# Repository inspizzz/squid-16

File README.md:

<div align="center">

# Squid-16

**An open-source, 16-channel dry-electrode EEG sensor on one 40 mm board.**

Eighteen spring-loaded pins, two 24-bit converters, an on-board ESP32-C3 and Bluetooth LE.
No gel, no cap, no separate controller.

<sub>3D render from the design files, not a photograph. No board has been built yet.</sub>

[Build one](docs/BUILD.md) · [How it works](docs/DESIGN.md) · [Simulation results](sim/results/report.md) · [Get one](#get-one) · [Cost](#what-it-costs)

</div>

> **Not a medical device.** This is an experimenter's board. It has no
> isolation from its power supply: wear it only while it runs from a battery or
> power bank, never while it is connected to a computer or a wall charger.

> **Status: revision B, not yet built.** The design passes KiCad's electrical
> and design-rule checks, the firmware compiles and passes its PC-side tests,
> and the wiring has been checked in simulation, but no board has been
> manufactured or powered. Expect to debug. There are no measured noise or
> performance figures yet. See
> [what has and has not been verified](#what-has-been-verified).

## What it is

| | |
|---|---|
| Channels | 16, plus a reference pin and a bias pin, in one 30 mm cluster |
| Electrodes | 18 surface-mount spring pins, 4 mm tip, 6.5 mm apart |
| Converters | 2 x TI ADS131M08, 24-bit, all channels sampled at the same instant |
| Sample rate | 250 samples/s nominal (8.192 MHz clock, highest oversampling setting; not yet measured) |
| Reference | Buffered by a low-noise op-amp (can be bypassed) |
| Processor and radio | Espressif ESP32-C3-WROOM-02 module, soldered on |
| Link | Bluetooth LE, one 51-byte packet per sample |
| Board | 40 mm round, 4 layers, 1.0 mm thick; parts on top, pins underneath |
| Power and flashing | USB-C on the board, 5 V from a power bank |

Squid-16 is an independent design inspired by the PiEEG "Octopus 16" idea of
putting the whole montage, reference included, on one small board. It shares no
design files or code with that product (which publishes neither schematics nor
a licence); it is drawn from the component datasheets. Its data stream uses the
same packet layout, so viewers written for that format can read it.
[How it differs](docs/DESIGN.md#how-it-differs-from-the-board-that-inspired-it).

This project is not affiliated with, endorsed by or supported by PiEEG.
"PiEEG" and "Octopus 16" are names used by their owner and appear here only
to say what inspired this design.

Revision A (32 mm, with a plug-in Seeed XIAO ESP32-S3 instead of an on-board
module) is kept under the git tag `rev-A`.

## Repository map

```
README.md            you are here
LICENSE              which licence covers what
docs/
  BUILD.md           order, assemble, flash, first signal: start here to make one
  DESIGN.md          how the circuit works, pin maps, limits, open questions
  img/               renders and layer pictures
hardware/
  squid16.kicad_pro / .kicad_sch / .kicad_pcb    open these in KiCad 9
  lib/               the two project footprints (spring pin, radio module) and a 3D model of the pin
  production/        ready-to-upload gerbers, BOM, placement files, schematic PDF
  scripts/           the design as code: one file in, schematic + board out
firmware/
  squid16/          PlatformIO project for the on-board ESP32-C3
  test/              PC-side tests of the driver against a simulated converter
software/
  squid16.py        record to CSV over Bluetooth
sim/
  run_all.py         simulate this board; results in sim/results/report.md
```

## Get one

**Nobody sells built Squid-16 boards.** This is a design you have made for
you. There are three ways to end up holding one:

| Route | What you do | Skill needed |
|---|---|---|
| **Have it built** (easiest) | Upload [`hardware/production/squid16-pcbway.zip`](hardware/production/squid16-pcbway.zip) to a turnkey assembler such as PCBWay. It contains the gerbers, a parts list with manufacturer part numbers, placement files and a notes file. They make the board, buy the parts and solder them. You flash the firmware over USB-C. | None beyond placing an order |
| **Have the top side built, fit the pins yourself** | Same package, ask for top side only. Solder the 18 spring pins with an ordinary iron (one large pad each). | Basic soldering |
| **Build it all yourself** | Order bare boards from the gerbers and follow [docs/BUILD.md](docs/BUILD.md). | Fine-pitch surface-mount soldering, hot air |

After that: plug in USB-C, run `pio run -t upload` in `firmware/squid16`,
power it from a power bank and run `python3 software/squid16.py`.
[docs/BUILD.md](docs/BUILD.md) has every step.

If you would rather buy a finished unit, open an issue saying so. There is no
promise that a batch will be made, but it is the only way interest gets
counted.

Because this revision is untested, order the minimum (five boards, two
assembled) and expect the first one to need debugging.

## What it costs

Figures for **five bare boards with two assembled**, the smallest sensible
order. The PCBWay figures are what its online calculator showed for this
design's gerbers on 10 November 2026, before their engineers' review; the rest
are estimates. Import VAT and duty are extra.

| Item | Cost (USD) | Source |
|---|---|---|
| 5 bare boards: 4 layers, 1.0 mm, ENIG, 5-day build | 62 | PCBWay calculator |
| Assembly labour, 2 boards, one or both sides | 88 | PCBWay calculator |
| Courier shipping | about 29, offset by a first-order discount at the time | PCBWay calculator |
| Components for 2 boards, excluding the spring pins | 80 - 110 | estimate from distributor prices |
| 36 Mill-Max spring pins (18 per board) | about 145 | DigiKey list price, about 4 each |
| **Two working boards, Mill-Max pins** | **about 375 - 405** | |
| **Per board** | **about 190 - 200** | |

Ways to spend less:

- Generic 4 x 11 mm surface-mount pogo pins fit the same pads and cost a
  small fraction of the Mill-Max part. Untested, like everything else here.
- Lead-free HASL instead of ENIG roughly halves the bare-board price (32
  instead of 62), at the cost of less flat pads.
- The three spare bare boards cost only parts to populate later.

## Change it

The whole board is generated from one Python file,
[`hardware/scripts/design.py`](hardware/scripts/design.py): every part, net and
position. Edit it and run

```
hardware/scripts/build.sh
```

to regenerate the schematic, place and route the board, run the checks and
write new fabrication files (needs KiCad 9 and numpy; routing takes 6 to 12
minutes). The router is a simple one written for this board and it does not
succeed every time: of three full rebuilds of this exact design, one connected
everything, and that is the board committed here. When it fails it says so and
puts the previous board back; run it again or nudge a part. You can also just
open the KiCad files and edit them by hand, but
then stop using the generator, because it overwrites them.

## What has been verified

| Check | Result |
|---|---|
| Schematic electrical rules (KiCad ERC, all severities) | 0 violations |
| Board design rules (KiCad DRC, all severities) | 0 violations, 0 unconnected |
| Schematic and board agree (DRC parity, plus a pin-by-pin netlist comparison with `design.py`) | 0 differences |
| Rebuilding the board from `design.py` gives a complete board every time | **no**: 1 of 3 attempts; the committed board is the complete one |
| Firmware driver and packet code against a simulated ADS131M08 (`firmware/test/run.sh`) | pass |
| Firmware builds for the ESP32-C3 (PlatformIO, Arduino core, NimBLE-Arduino) | builds, 753 kB flash |
| Recorder packet decoder (`squid16.py --selftest`) | pass |
| Wiring traced from the PCB copper against the firmware's pins and channel order ([simulation](sim/results/report.md)) | 16 of 16 channels in the right place |
| A manufactured board | **not done** |
| Firmware on real hardware, Bluetooth range and throughput, noise, signal quality | **not done** |

## Licence

Hardware: CERN-OHL-P-2.0. Firmware and software: MIT. Documentation: CC-BY-4.0.
See [LICENSE](LICENSE). You may build, change and sell it.

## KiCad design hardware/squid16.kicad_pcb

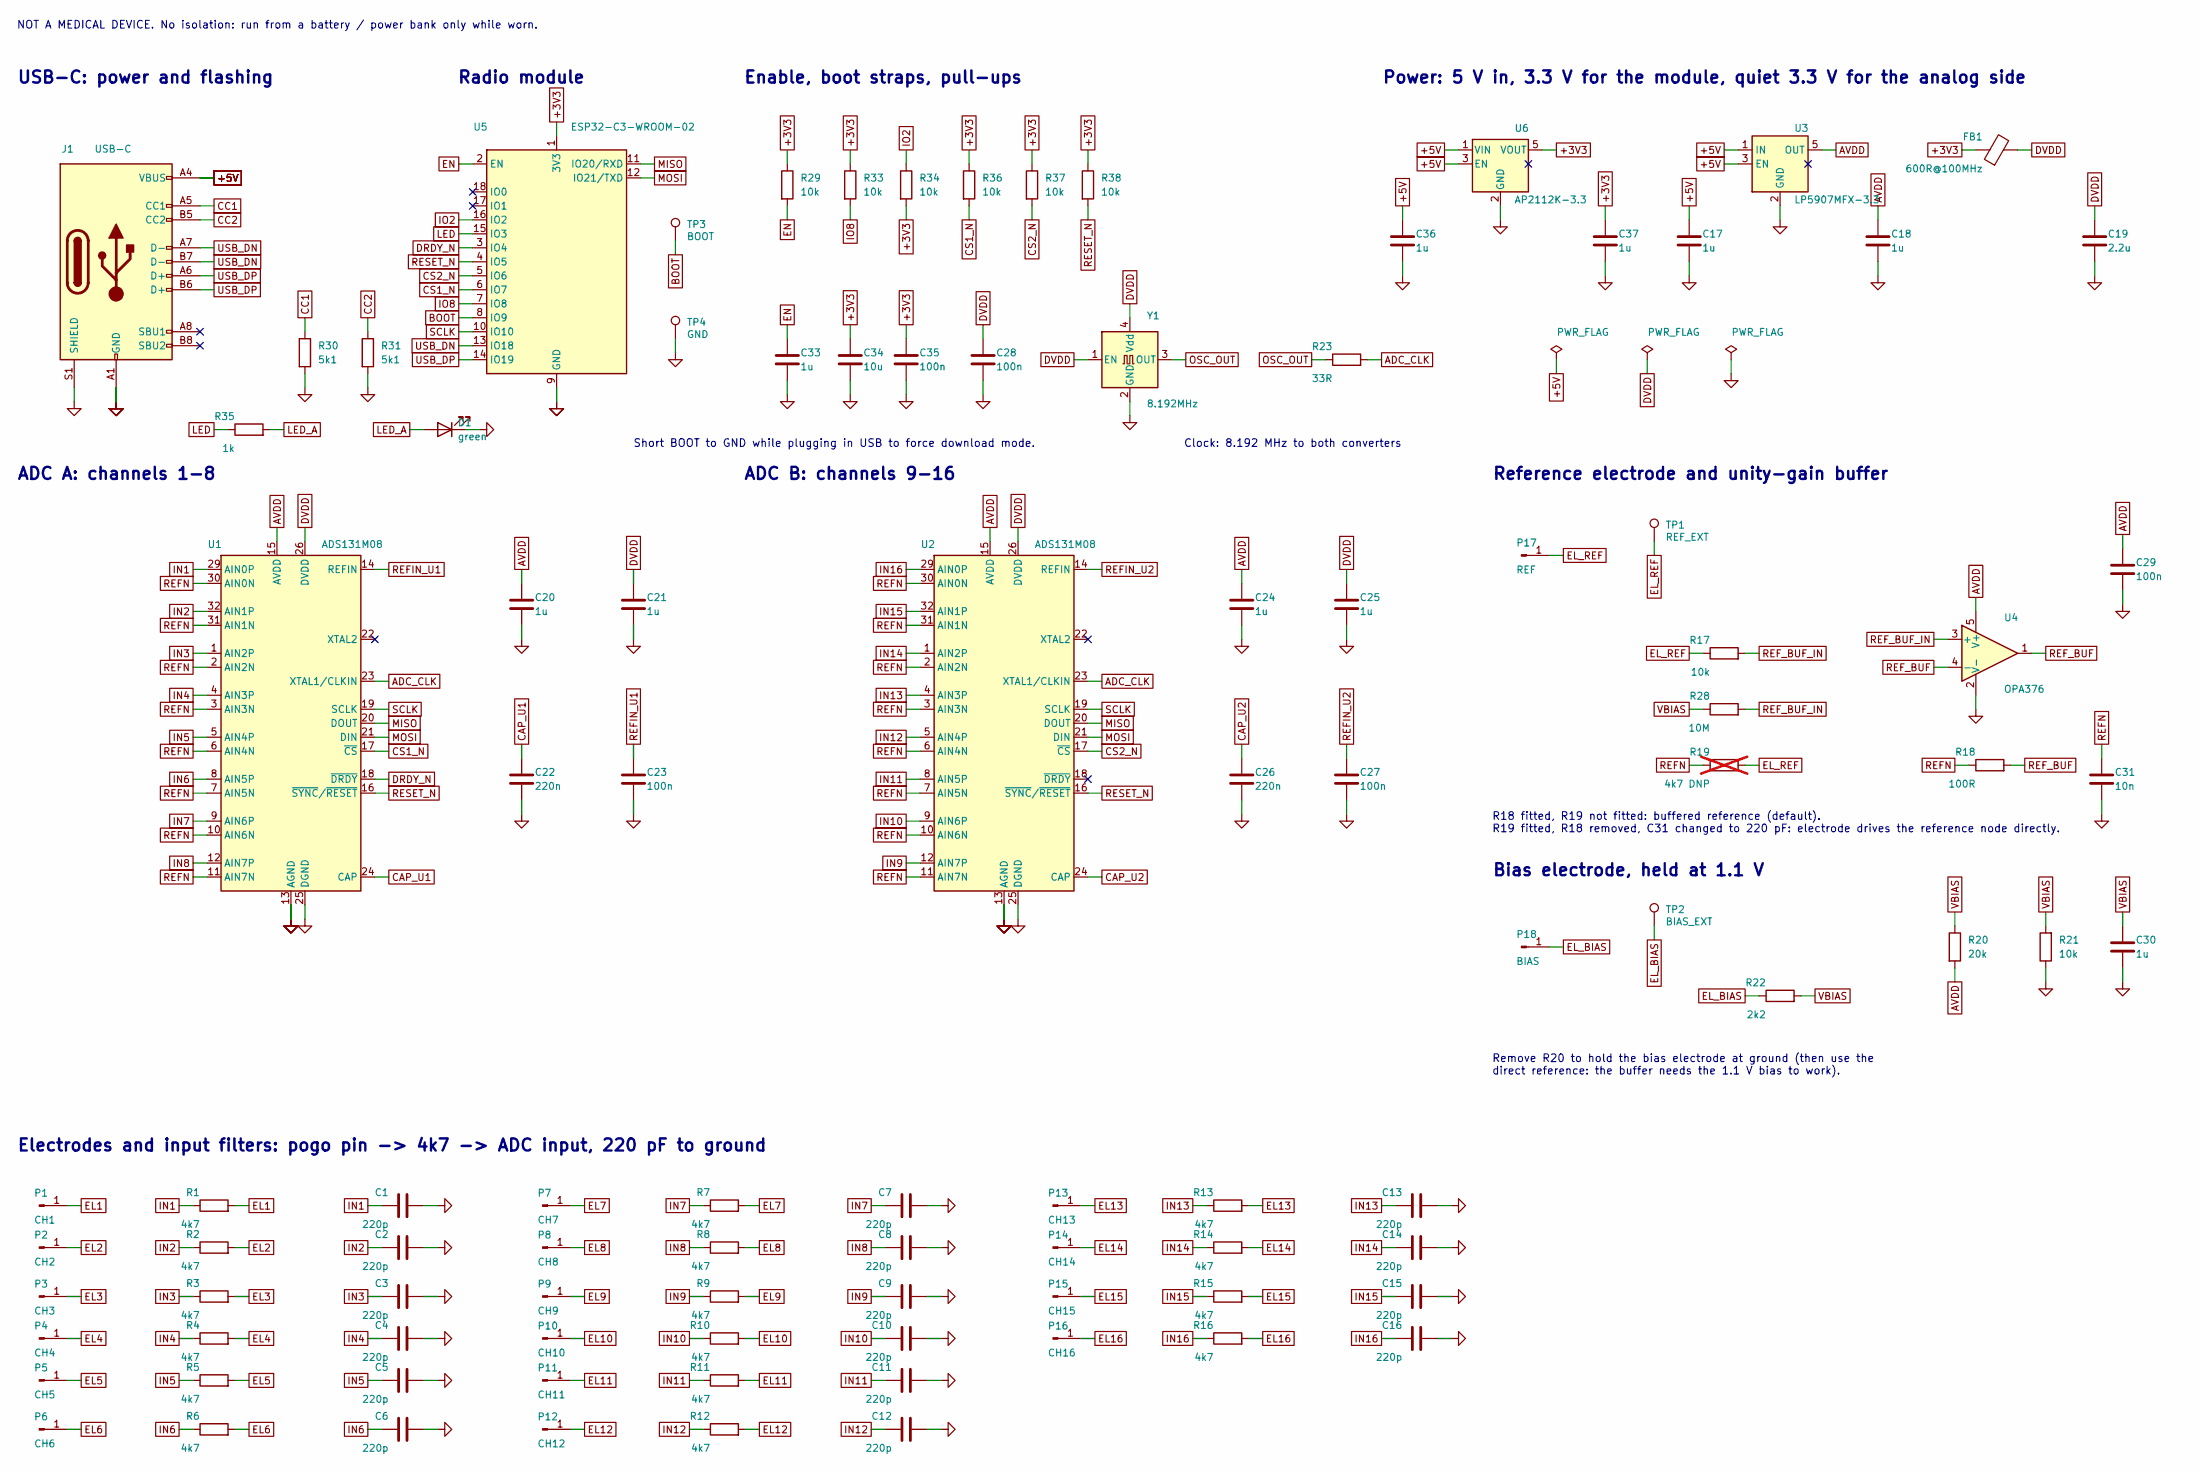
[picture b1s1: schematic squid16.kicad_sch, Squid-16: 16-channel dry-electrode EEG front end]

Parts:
C1, C2, C3, C4, C5, C6, C7, C8, C9, C10, C11, C12, C13, C14, C15, C16: 220p; C_0402_1005Metric
C17, C18, C20, C21, C24, C25, C30, C33, C36, C37: 1u; C_0402_1005Metric
C19: 2.2u; C_0402_1005Metric
C22, C26: 220n; C_0402_1005Metric
C23, C27, C28, C29, C35: 100n; C_0402_1005Metric
C31: 10n; C_0402_1005Metric
C34: 10u; C_0603_1608Metric
D1: green; LED_0402_1005Metric; MPN generic 0402 green LED
FB1: 600R@100MHz; L_0402_1005Metric; MPN BLM15AG601SN1D
J1: USB-C; USB_C_Receptacle_GCT_USB4110; MPN USB4110-GF-A
P1: CH1; PogoPin_MillMax_0845_SMD; MPN 0845-0-15-20-52-14-11-0
P2: CH2; PogoPin_MillMax_0845_SMD; MPN 0845-0-15-20-52-14-11-0
P3: CH3; PogoPin_MillMax_0845_SMD; MPN 0845-0-15-20-52-14-11-0
P4: CH4; PogoPin_MillMax_0845_SMD; MPN 0845-0-15-20-52-14-11-0
P5: CH5; PogoPin_MillMax_0845_SMD; MPN 0845-0-15-20-52-14-11-0
P6: CH6; PogoPin_MillMax_0845_SMD; MPN 0845-0-15-20-52-14-11-0
P7: CH7; PogoPin_MillMax_0845_SMD; MPN 0845-0-15-20-52-14-11-0
P8: CH8; PogoPin_MillMax_0845_SMD; MPN 0845-0-15-20-52-14-11-0
P9: CH9; PogoPin_MillMax_0845_SMD; MPN 0845-0-15-20-52-14-11-0
P10: CH10; PogoPin_MillMax_0845_SMD; MPN 0845-0-15-20-52-14-11-0
P11: CH11; PogoPin_MillMax_0845_SMD; MPN 0845-0-15-20-52-14-11-0
P12: CH12; PogoPin_MillMax_0845_SMD; MPN 0845-0-15-20-52-14-11-0
P13: CH13; PogoPin_MillMax_0845_SMD; MPN 0845-0-15-20-52-14-11-0
P14: CH14; PogoPin_MillMax_0845_SMD; MPN 0845-0-15-20-52-14-11-0
P15: CH15; PogoPin_MillMax_0845_SMD; MPN 0845-0-15-20-52-14-11-0
P16: CH16; PogoPin_MillMax_0845_SMD; MPN 0845-0-15-20-52-14-11-0
P17: REF; PogoPin_MillMax_0845_SMD; MPN 0845-0-15-20-52-14-11-0
P18: BIAS; PogoPin_MillMax_0845_SMD; MPN 0845-0-15-20-52-14-11-0
R1, R2, R3, R4, R5, R6, R7, R8, R9, R10, R11, R12, R13, R14, R15, R16: 4k7; R_0402_1005Metric
R17, R21, R29, R33, R34, R36, R37, R38: 10k; R_0402_1005Metric
R18: 100R; R_0402_1005Metric
R19: 4k7 DNP; R_0402_1005Metric; not fitted
R20: 20k; R_0402_1005Metric
R22: 2k2; R_0402_1005Metric
R23: 33R; R_0402_1005Metric
R28: 10M; R_0402_1005Metric
R30, R31: 5k1; R_0402_1005Metric
R35: 1k; R_0402_1005Metric
TP1: REF_EXT; TestPoint_Pad_D1.0mm
TP2: BIAS_EXT; TestPoint_Pad_D1.0mm
TP3: BOOT; TestPoint_Pad_D1.0mm
TP4: GND; TestPoint_Pad_D1.0mm
U1, U2: ADS131M08; TQFP-32_5x5mm_P0.5mm; MPN ADS131M08IPBSR
U3: LP5907MFX-3.3; SOT-23-5; MPN LP5907MFX-3.3/NOPB
U4: OPA376; SOT-23-5; MPN OPA376AIDBVR
U5: ESP32-C3-WROOM-02; ESP32-C3-WROOM-02_NoVias; MPN ESP32-C3-WROOM-02-N4
U6: AP2112K-3.3; SOT-23-5; MPN AP2112K-3.3TRG1
Y1: 8.192MHz; Oscillator_SMD_SiT_PQFN-4Pin_2.5x2.0mm; MPN SiT1602BC-11-33E-8.192000

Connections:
+3V3: C34.2, C35.2, C37.1, FB1.1, R29.1, R33.1, R34.2, R36.1, R37.1, R38.1, U5.1 (3V3), U6.5 (VOUT)
+5V: C17.2, C36.2, J1.A4 (VBUS), J1.A9 (VBUS), J1.B4 (VBUS), J1.B9 (VBUS), U3.1 (IN), U3.3 (EN), U6.1 (VIN), U6.3 (EN)
ADC_CLK: R23.2, U1.23 (XTAL1/CLKIN), U2.23 (XTAL1/CLKIN)
AVDD: C18.1, C20.1, C24.1, C29.2, R20.2, U1.15 (AVDD), U2.15 (AVDD), U3.5 (OUT), U4.5 (V+)
BOOT: TP3.1, U5.8 (IO9)
CAP_U1: C22.1, U1.24 (CAP)
CAP_U2: C26.1, U2.24 (CAP)
CC1: J1.A5 (CC1), R30.1
CC2: J1.B5 (CC2), R31.1
CS1_N: R36.2, U1.17 (~CS), U5.6 (IO7)
CS2_N: R37.2, U2.17 (~CS), U5.5 (IO6)
DRDY_N: U1.18 (~DRDY), U5.3 (IO4)
DVDD: C19.1, C21.1, C25.1, C28.1, FB1.2, U1.26 (DVDD), U2.26 (DVDD), Y1.1 (EN), Y1.4 (Vdd)
EL1: P1.1, R1.2
EL2: P2.1, R2.2
EL3: P3.1, R3.2
EL4: P4.1, R4.2
EL5: P5.1, R5.2
EL6: P6.1, R6.2
EL7: P7.1, R7.2
EL8: P8.1, R8.2
EL9: P9.1, R9.2
EL10: P10.1, R10.2
EL11: P11.1, R11.2
EL12: P12.1, R12.2
EL13: P13.1, R13.2
EL14: P14.1, R14.2
EL15: P15.1, R15.2
EL16: P16.1, R16.2
EL_BIAS: P18.1, R22.1, TP2.1
EL_REF: P17.1, R17.1, R19.2, TP1.1
EN: C33.2, R29.2, U5.2 (EN)
GND: C1.2, C2.2, C3.2, C4.2, C5.2, C6.2, C7.2, C8.2, C9.2, C10.2, C11.2, C12.2, C13.2, C14.2, C15.2, C16.2, C17.1, C18.2, C19.2, C20.2, C21.2, C22.2, C23.2, C24.2, C25.2, C26.2, C27.2, C28.2, C29.1, C30.2, C31.2, C33.1, C34.1, C35.1, C36.1, C37.2, D1.1 (K), J1.A1 (GND), J1.A12 (GND), J1.B1 (GND), J1.B12 (GND), J1.S1 (SHIELD), R21.1, R30.2, R31.2, TP4.1, U1.13 (AGND), U1.25 (DGND), U1.27 (AGND), U1.28 (AGND), U2.13 (AGND), U2.25 (DGND), U2.27 (AGND), U2.28 (AGND), U3.2 (GND), U4.2 (V-), U5.9 (GND), U5.19 (GND), U6.2 (GND), Y1.2 (GND)
IN1: C1.1, R1.1, U1.29 (AIN0P)
IN2: C2.1, R2.1, U1.32 (AIN1P)
IN3: C3.1, R3.1, U1.1 (AIN2P)
IN4: C4.1, R4.1, U1.4 (AIN3P)
IN5: C5.1, R5.1, U1.5 (AIN4P)
IN6: C6.1, R6.1, U1.8 (AIN5P)
IN7: C7.1, R7.1, U1.9 (AIN6P)
IN8: C8.1, R8.1, U1.12 (AIN7P)
IN9: C9.1, R9.1, U2.12 (AIN7P)
IN10: C10.1, R10.1, U2.9 (AIN6P)
IN11: C11.1, R11.1, U2.8 (AIN5P)
IN12: C12.1, R12.1, U2.5 (AIN4P)
IN13: C13.1, R13.1, U2.4 (AIN3P)
IN14: C14.1, R14.1, U2.1 (AIN2P)
IN15: C15.1, R15.1, U2.32 (AIN1P)
IN16: C16.1, R16.1, U2.29 (AIN0P)
IO2: R34.1, U5.16 (IO2)
IO8: R33.2, U5.7 (IO8)
LED: R35.1, U5.15 (IO3)
LED_A: D1.2 (A), R35.2
MISO: U1.20 (DOUT), U2.20 (DOUT), U5.11 (IO20/RXD)
MOSI: U1.21 (DIN), U2.21 (DIN), U5.12 (IO21/TXD)
OSC_OUT: R23.1, Y1.3 (OUT)
REFIN_U1: C23.1, U1.14 (REFIN)
REFIN_U2: C27.1, U2.14 (REFIN)
REFN: C31.1, R18.1, R19.1, U1.2 (AIN2N), U1.3 (AIN3N), U1.6 (AIN4N), U1.7 (AIN5N), U1.10 (AIN6N), U1.11 (AIN7N), U1.30 (AIN0N), U1.31 (AIN1N), U2.2 (AIN2N), U2.3 (AIN3N), U2.6 (AIN4N), U2.7 (AIN5N), U2.10 (AIN6N), U2.11 (AIN7N), U2.30 (AIN0N), U2.31 (AIN1N)
REF_BUF: R18.2, U4.1, U4.4 (-)
REF_BUF_IN: R17.2, R28.2, U4.3 (+)
RESET_N: R38.2, U1.16 (~SYNC/~RESET), U2.16 (~SYNC/~RESET), U5.4 (IO5)
SCLK: U1.19 (SCLK), U2.19 (SCLK), U5.10 (IO10)
USB_DN: J1.A7 (D-), J1.B7 (D-), U5.13 (IO18)
USB_DP: J1.A6 (D+), J1.B6 (D+), U5.14 (IO19)
VBIAS: C30.1, R20.1, R21.2, R22.2, R28.1

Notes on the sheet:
USB-C: power and flashing
Radio module
Enable, boot straps, pull-ups
Power: 5 V in, 3.3 V for the module, quiet 3.3 V for the analog side
ADC A: channels 1-8
ADC B: channels 9-16
Reference electrode and unity-gain buffer
Bias electrode, held at 1.1 V
Electrodes and input filters: pogo pin -> 4k7 -> ADC input, 220 pF to ground
Clock: 8.192 MHz to both converters
Short BOOT to GND while plugging in USB to force download mode.
R18 fitted, R19 not fitted: buffered reference (default). R19 fitted, R18 removed, C31 changed to 220 pF: electrode drives the reference node directly.
Remove R20 to hold the bias electrode at ground (then use the direct reference: the buffer needs the 1.1 V bias to work).
NOT A MEDICAL DEVICE. No isolation: run from a battery / power bank only while worn.

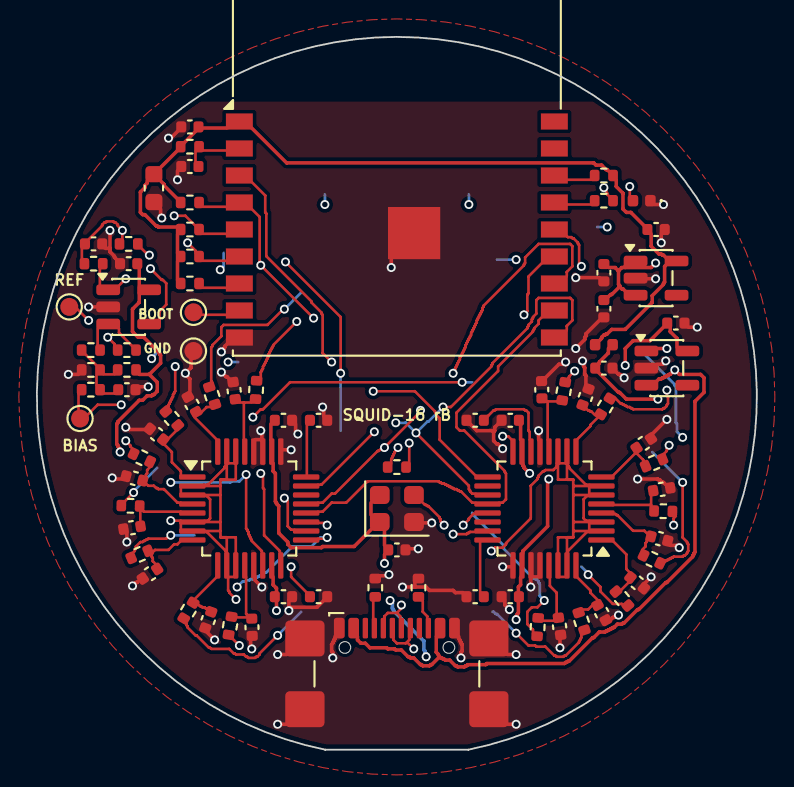
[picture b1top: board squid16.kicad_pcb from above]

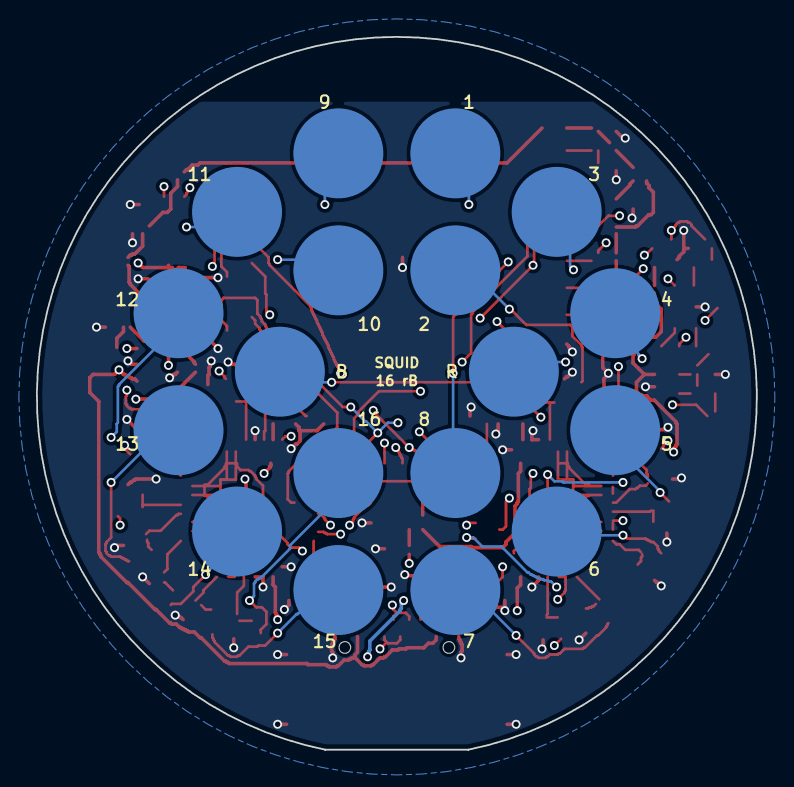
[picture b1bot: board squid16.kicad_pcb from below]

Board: 4 copper layers, 40.0 x 39.6 mm, 101 parts (18 on the bottom side), 66 nets.

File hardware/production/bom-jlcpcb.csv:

Comment,Designator,Footprint,LCSC Part #
220p (Capacitor 220 pF C0G 0402),"C1,C2,C3,C4,C5,C6,C7,C8,C9,C10,C11,C12,C13,C14,C15,C16",C_0402_1005Metric,
1u (Capacitor 1 uF X5R 10 V 0402),"C17,C18,C20,C21,C24,C25,C30,C33,C36,C37",C_0402_1005Metric,
2.2u (Capacitor 2.2 uF X5R 6.3 V 0402),C19,C_0402_1005Metric,
220n (Capacitor 220n 0402),"C22,C26",C_0402_1005Metric,
100n (Capacitor 100n 0402),"C23,C27,C28,C29,C35",C_0402_1005Metric,
10n (Capacitor 10 nF C0G 0402),C31,C_0402_1005Metric,
10u (Capacitor 10 uF X5R 6.3 V 0603),C34,C_0603_1608Metric,
generic 0402 green LED,D1,LED_0402_1005Metric,
BLM15AG601SN1D,FB1,L_0402_1005Metric,
USB4110-GF-A,J1,USB_C_Receptacle_GCT_USB4110,
4k7 (Resistor 4k7 1% 0402),"R1,R2,R3,R4,R5,R6,R7,R8,R9,R10,R11,R12,R13,R14,R15,R16",R_0402_1005Metric,
10k (Resistor 10k 1% 0402),"R17,R21,R29,R36,R37,R38",R_0402_1005Metric,
100R (Resistor 100R 0402. Fitted: reference node driven by the buffer),R18,R_0402_1005Metric,
20k (Resistor 20k 1% 0402. Remove to hold the bias electrode at ground instead of 1.1 V),R20,R_0402_1005Metric,
2k2 (Resistor 2k2 1% 0402),R22,R_0402_1005Metric,
33R (Resistor 33R 1% 0402),R23,R_0402_1005Metric,
10M (Resistor 10M 0402: holds the buffer input at the bias voltage when the reference pin is not touching),R28,R_0402_1005Metric,
"5k1 (Resistor 5k1 1% 0402, USB-C sink ID)","R30,R31",R_0402_1005Metric,
"10k (Resistor 10k 0402, boot strap pull-up)","R33,R34",R_0402_1005Metric,
1k (Resistor 1k 1% 0402),R35,R_0402_1005Metric,
ADS131M08IPBSR,"U1,U2",TQFP-32_5x5mm_P0.5mm,
LP5907MFX-3.3/NOPB,U3,SOT-23-5,
OPA376AIDBVR,U4,SOT-23-5,
ESP32-C3-WROOM-02-N4,U5,ESP32-C3-WROOM-02_NoVias,
AP2112K-3.3TRG1,U6,SOT-23-5,
SiT1602BC-11-33E-8.192000,Y1,Oscillator_SMD_SiT_PQFN-4Pin_2.5x2.0mm,

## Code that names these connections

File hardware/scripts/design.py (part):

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            "17": cs, "18": drdy, "16": "RESET_N"}
    for k, ch in ain_to_ch.items():
        pins[AIN_P[k]] = f"IN{ch}"
        pins[AIN_N[k]] = "REFN"
    x, y = ADC_XY[ref]
    add(ref, ADS, "ADS131M08", TQFP, pins, (x, y, rot), mpn="ADS131M08IPBSR",
        mfr="Texas Instruments", desc="8-channel 24-bit simultaneous-sampling delta-sigma ADC")
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
# ---- reference electrode and its buffer (left of the module) -------------------
x, y = electrode_xy("REF")
add("P17", "Connector:Conn_01x01_Pin", "REF", POGO, {"1": "EL_REF"}, (x, y, 0),
    side="bottom", mpn="0845-0-15-20-52-14-11-0", mfr="Mill-Max", hand=True,
    desc="SMD spring-loaded pin, 3.96 mm tip (dry electrode)")
add("TP1", "Connector:TestPoint", "REF_EXT", TP10,
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
# ---- bias electrode held at 1.1 V -------------------------------------------------
x, y = electrode_xy("BIAS")
add("P18", "Connector:Conn_01x01_Pin", "BIAS", POGO, {"1": "EL_BIAS"}, (x, y, 0),
    side="bottom", mpn="0845-0-15-20-52-14-11-0", mfr="Mill-Max", hand=True,
    desc="SMD spring-loaded pin, 3.96 mm tip (dry electrode)")
add("TP2", "Connector:TestPoint", "BIAS_EXT", TP10,
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

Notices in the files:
hardware/squid16.kicad_sch:
Open hardware, CERN-OHL-P-2.0
